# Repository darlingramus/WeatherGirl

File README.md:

# WeatherGirl
**Complete weather station** on clean **ATmega328P**.

**Project includes:**
- code in **C** for **PlatformIO**
- projects' pcb in **KiCad**
- Sensors: BME280, OLED SSD1306, DS3231-RTC and TTP223

## Used components
`| Microcontroler | ATmega328P`

`| Sensor temp/pres/hum | BME280`

`| OLED display | OLED SSD1106`

`| DS3231 clock | RTC`

`| Pull-up resistor | 10kΩ`

`| Capacitors | 100nF x 3 | 100uF`

`| ISP programmer | 6-pin (2x3) `

`| Power supply | Screw terminal | 5V` 

`| Stabilizer | AMS1117 5V to 3V3`

## Software requirements

- **PlatformIO** (extention to VSCode or CLion)
- **ISP Programmer**
- **KiCad 10.0** – if you want to check/add something

# Software

## Install and boot

### Step 1: clone repo
```bash
git clone https://github.com/darlingramus/WeatherGirl.git
cd WeatherGirl
```
### Step 2: 
- Open VSCode/Clion
- Install PlatformIO extention
- Open folder WeatherGirl (PlatformIO will find the project automaticaly)

### Step 3: Configure `platformio.ini`
```bash
[env:ATmega328P]
platform = atmelavr
board = ATmega328P
framework = baremetal
upload_protocol = AVRISP
debug_tool = AVRISP
```
### Step 4: Connect ISP programmer
### Step 5: Compile and upload code
PlatformIO: Click upload button

# Hardware - KiCad
PCB designed in KiCad 10.0

## Schematic

## Front PCB

## Back PCB

## How to open in KiCad
Install KiCad
Open hardware/kicad/WeatherGirl.kicad_pro

## License
[MIT](https://choosealicense.com/licenses/mit/)

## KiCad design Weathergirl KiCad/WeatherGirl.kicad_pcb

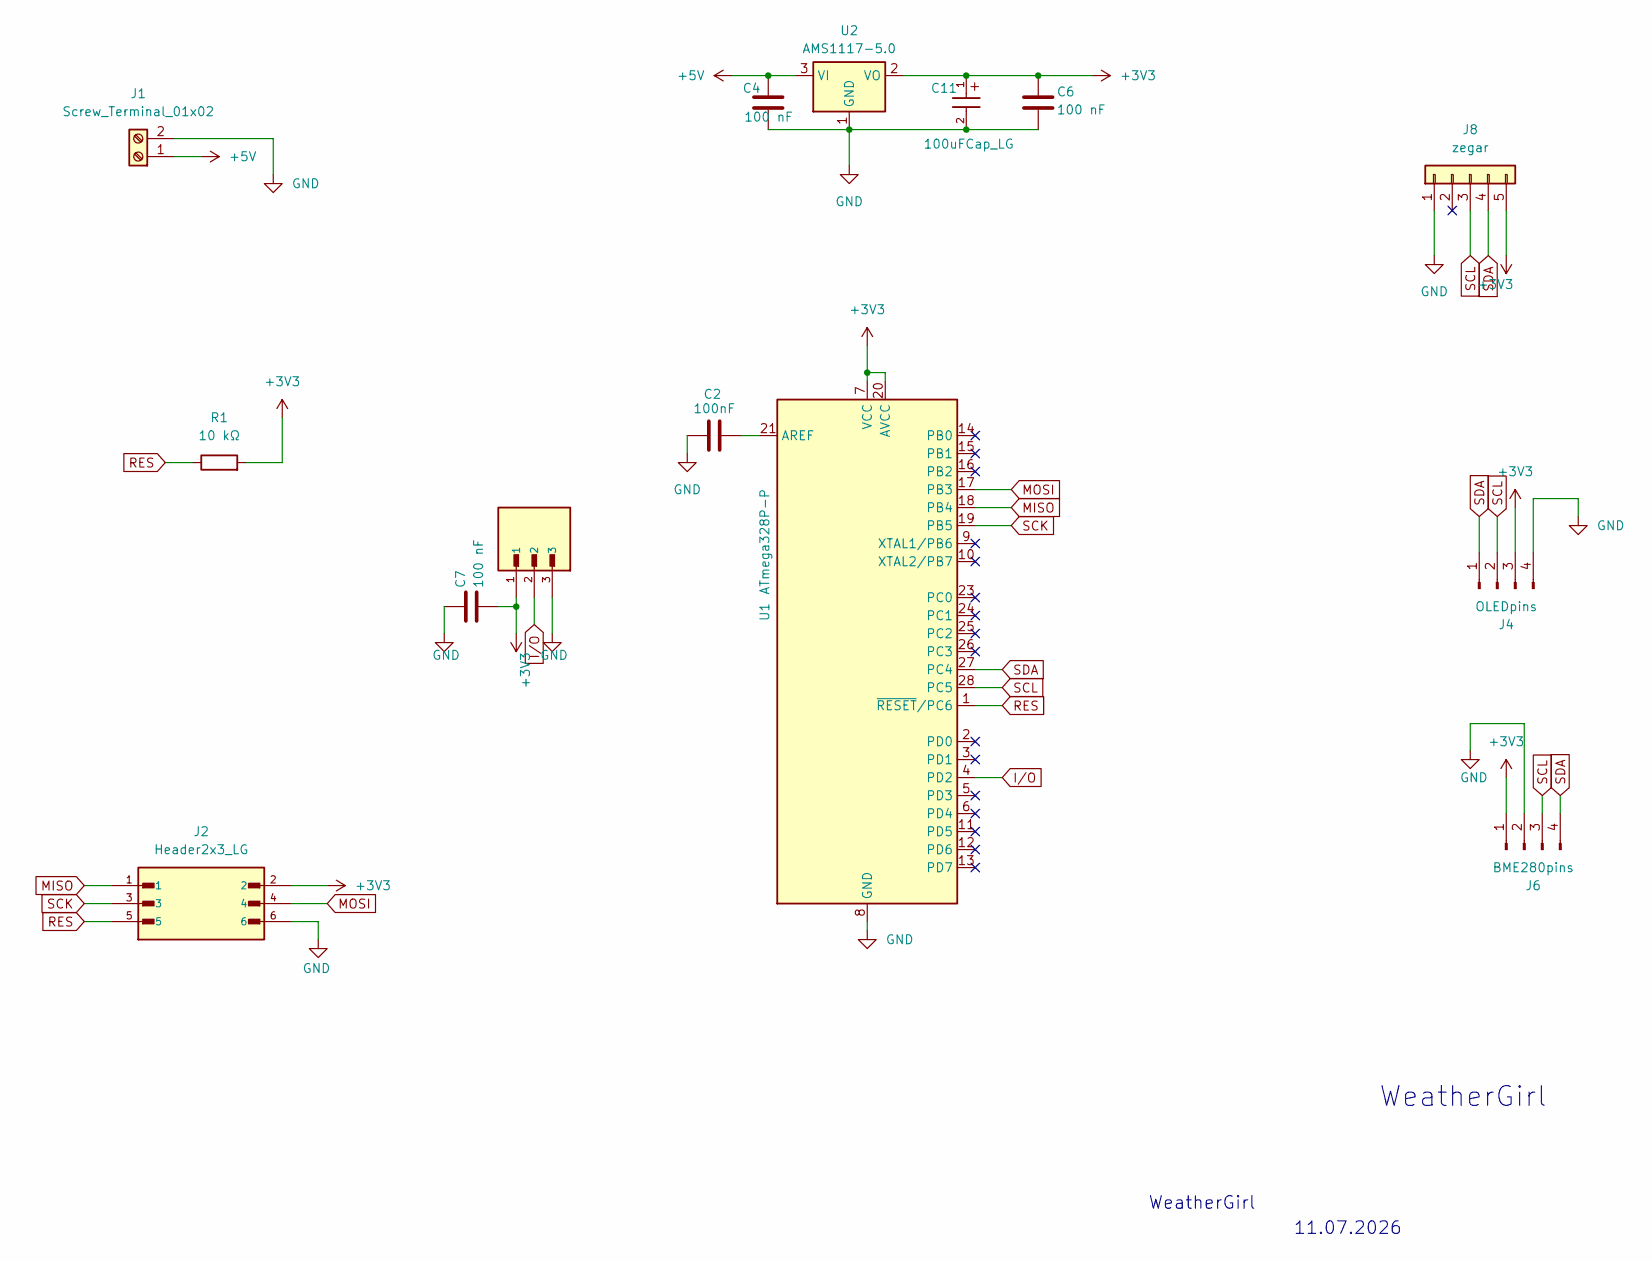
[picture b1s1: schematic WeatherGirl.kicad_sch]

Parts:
C2: 100nF; C_1206_3216Metric
C4, C6, C7: 100 nF; C_1206_3216Metric
C11: 100uFCap_LG; 100uFCap_MOD
J1: Screw_Terminal_01x02; TerminalBlock_MaiXu_MX126-5.0-02P_1x02_P5.00mm
J2: Header2x3_LG; PinHeader_2x03_P2.54mm_Vertical
J4: OLEDpins; PinHeader_1x04_P2.54mm_Vertical
J6: BME280pins; PinHeader_1x04_P2.54mm_Vertical
J7: Kanda01x03_LG; PinHeader_1x03_P2.54mm_Vertical; PARTREV 003.001
J8: zegar; PinHeader_1x05_P2.54mm_Vertical
R1: 10 kΩ; R_1206_3216Metric
U1: ATmega328P-P; DIP-28_W7.62mm
U2: AMS1117-5.0; SOT-223-3_TabPin2

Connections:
+3V3: C6.1, C7.2, C11.1, J2.2, J4.3, J6.1, J7.1, J8.5, R1.2, U1.7 (VCC), U1.20 (AVCC), U2.2 (VO)
+5V: C4.2, J1.1, U2.3 (VI)
GND: C2.2, C4.1, C6.2, C7.1, C11.2, J1.2, J2.6, J4.4, J6.2, J7.3, J8.1, U1.8 (GND), U1.22 (GND), U2.1 (GND)
I/O: J7.2, U1.4 (PD2)
MISO: J2.1, U1.18 (PB4)
MOSI: J2.4, U1.17 (PB3)
unnamed: C2.1, U1.21 (AREF)
RES: J2.5, R1.1, U1.1 (~RESET/PC6)
SCK: J2.3, U1.19 (PB5)
SCL: J4.2, J6.3, J8.3, U1.28 (PC5)
SDA: J4.1, J6.4, J8.4, U1.27 (PC4)

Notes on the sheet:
WeatherGirl
11.07.2026

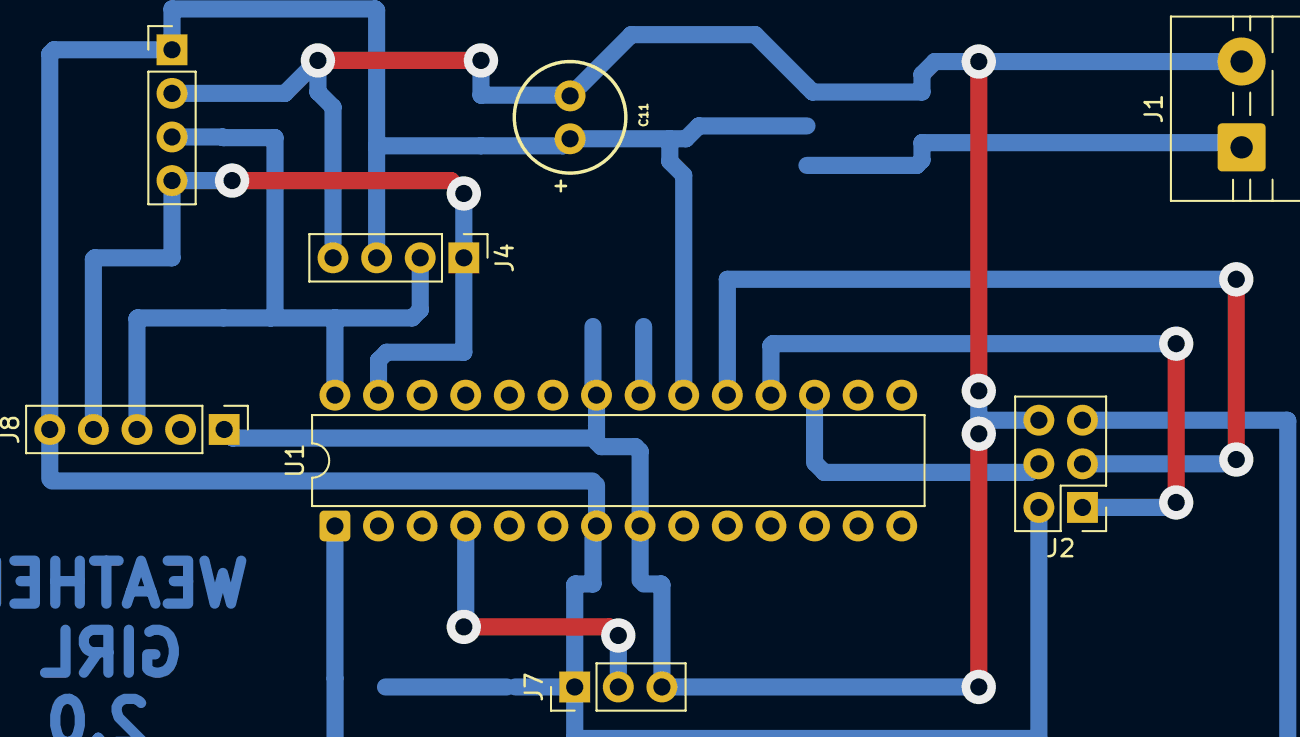
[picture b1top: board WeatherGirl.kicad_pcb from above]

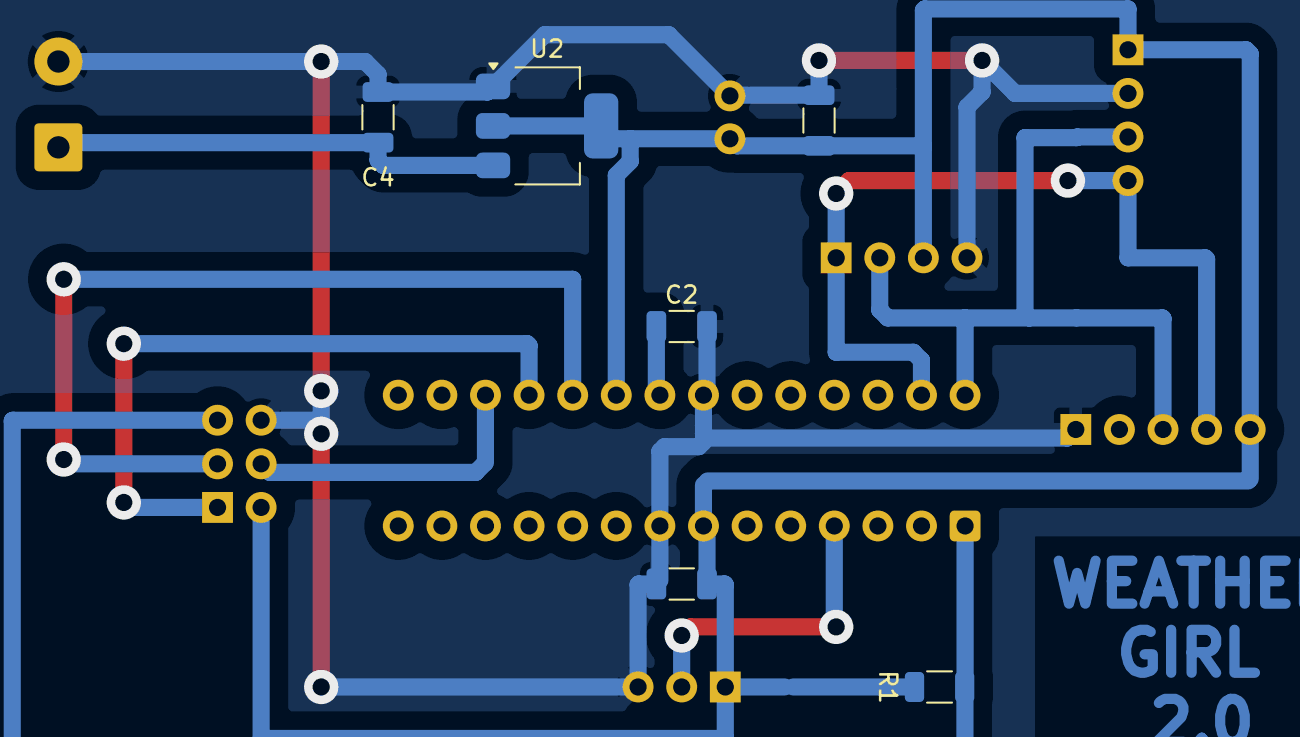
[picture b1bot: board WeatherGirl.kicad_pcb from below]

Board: 2 copper layers, 14 parts (6 on the bottom side), 11 nets.

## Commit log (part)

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2026-06-23 WeatherGirlCode
